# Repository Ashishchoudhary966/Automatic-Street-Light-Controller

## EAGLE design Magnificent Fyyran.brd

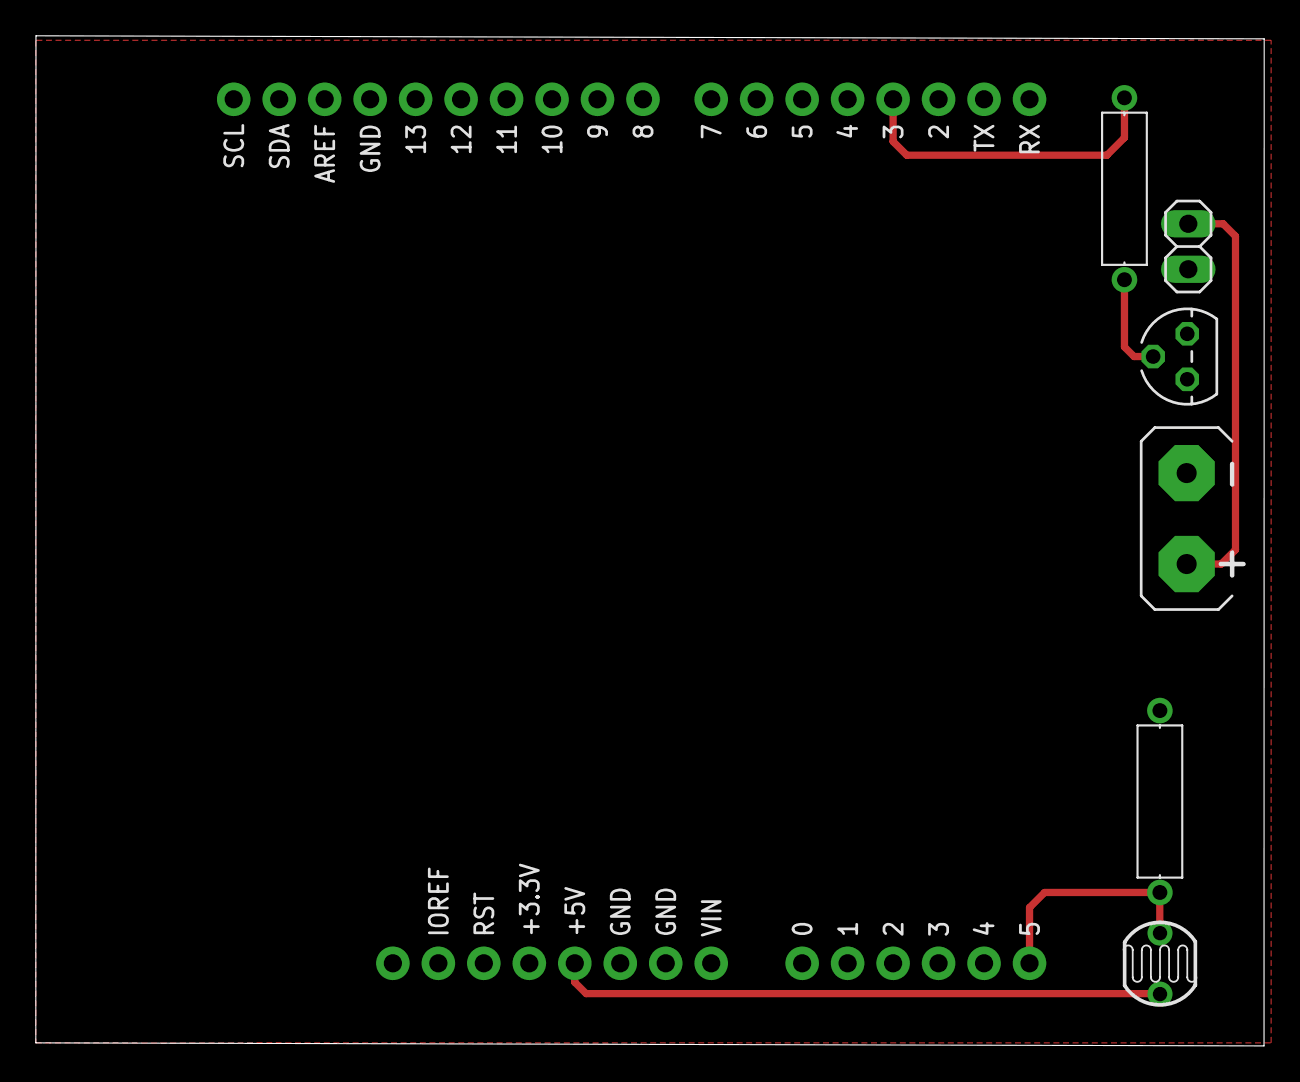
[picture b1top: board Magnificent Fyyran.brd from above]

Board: 2 copper layers, 68.6 x 56.4 mm, 7 parts (0 on the bottom side), 6 nets.

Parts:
L1: LIGHTBULB; 1X02
P1: BATTERYGENERIC; BATTERY-GENERIC
R1: PHOTOCELL_GL5528; GL5528
R2, R3: 1k; RESAD1016W63L850D250B
T1: NPN; TO92
U1: ARDUINO-UNO-R3-SHIELD

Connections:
GND: L1.1, P1.-, R2.1, T1.1, T1.3, U1.GND@0, U1.GND@1, U1.GND@2
P1+: L1.2, P1.+
T1_B: R3.2, T1.2
U1_5V: R1.2, U1.5V
U1_A5: R1.1, R2.2, U1.A5
U1_D3: R3.1, U1.D3
